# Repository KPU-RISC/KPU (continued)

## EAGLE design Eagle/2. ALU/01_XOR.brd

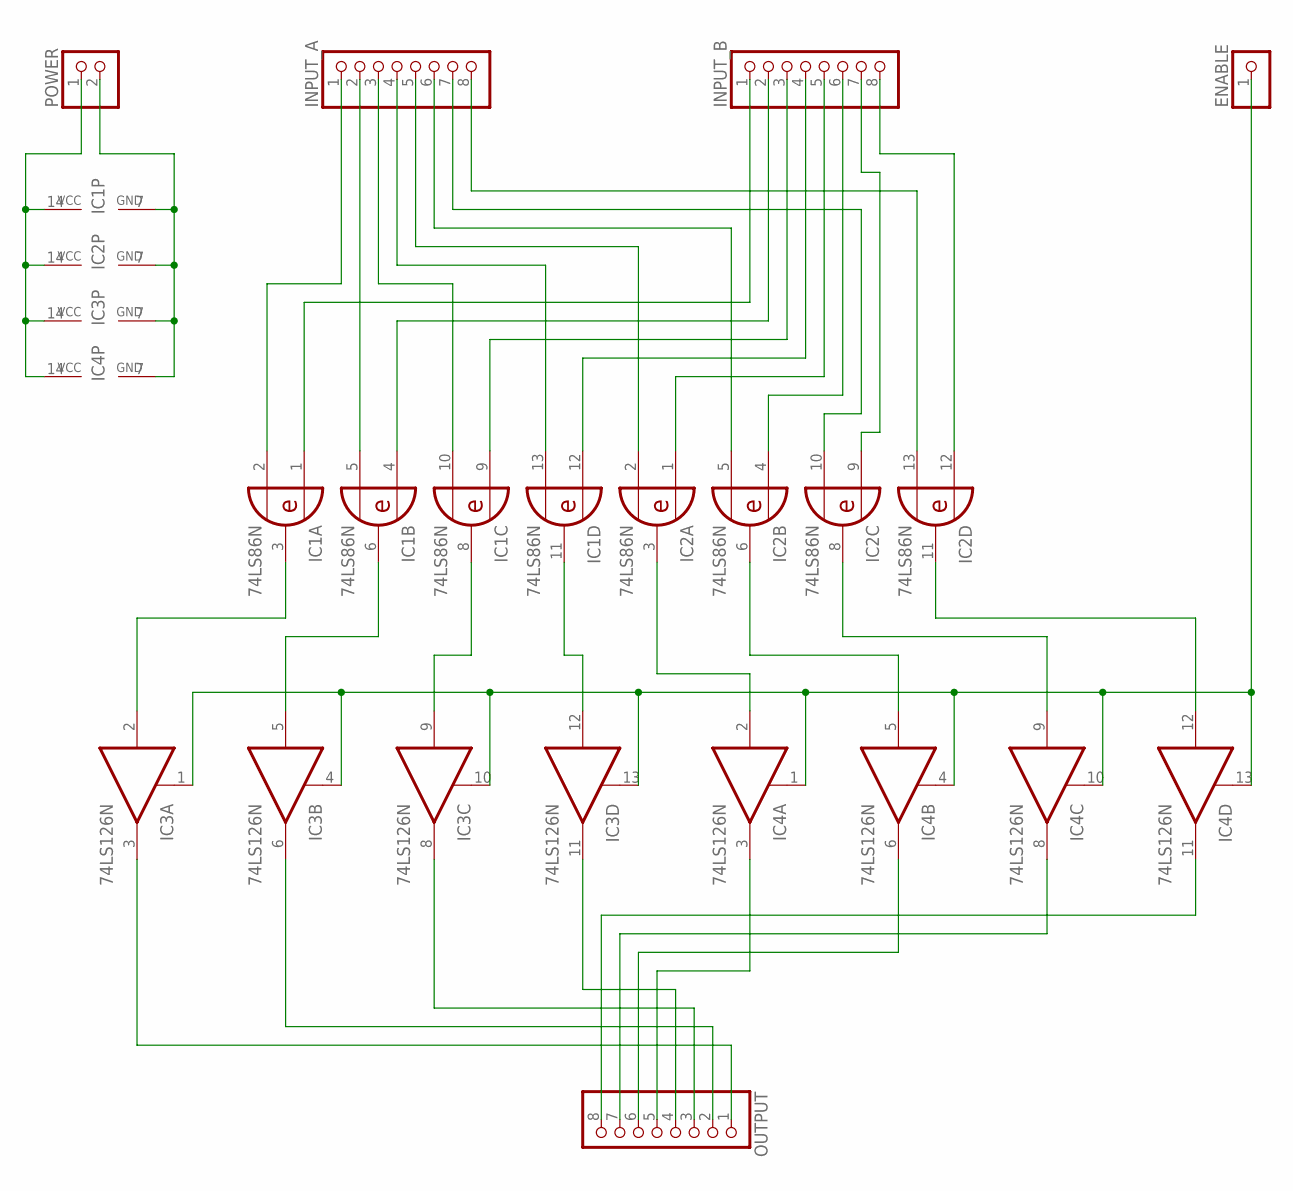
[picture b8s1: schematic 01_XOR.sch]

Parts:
ENABLE: PINHD-1X1; 1X01
IC1, IC2: 74LS86N; DIL14
IC3, IC4: 74LS126N; DIL14
INPUT_A: PINHD-1X8; 1X08
INPUT_B: PINHD-1X8; 1X08
OUTPUT: PINHD-1X8; 1X08
POWER: PINHD-1X2; 1X02

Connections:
GND: IC1.7 (GND), IC2.7 (GND), IC3.7 (GND), IC4.7 (GND), POWER.2
unnamed: IC1.2 (I1), INPUT_A.1
unnamed: IC1.1 (I0), INPUT_B.1
unnamed: IC1.5 (I1), INPUT_A.2
unnamed: IC1.4 (I0), INPUT_B.2
unnamed: IC1.10 (I1), INPUT_A.3
unnamed: IC1.9 (I0), INPUT_B.3
unnamed: IC1.13 (I1), INPUT_A.4
unnamed: IC1.12 (I0), INPUT_B.4
unnamed: IC2.2 (I1), INPUT_A.5
unnamed: IC2.1 (I0), INPUT_B.5
unnamed: IC2.5 (I1), INPUT_A.6
unnamed: IC2.4 (I0), INPUT_B.6
unnamed: IC2.10 (I1), INPUT_A.7
unnamed: IC2.9 (I0), INPUT_B.7
unnamed: IC2.13 (I1), INPUT_A.8
unnamed: IC2.12 (I0), INPUT_B.8
unnamed: IC1.3 (O), IC3.2 (I)
unnamed: IC1.6 (O), IC3.5 (I)
unnamed: IC1.8 (O), IC3.9 (I)
unnamed: IC1.11 (O), IC3.12 (I)
unnamed: IC2.3 (O), IC4.2 (I)
unnamed: IC2.6 (O), IC4.5 (I)
unnamed: IC2.8 (O), IC4.9 (I)
unnamed: IC2.11 (O), IC4.12 (I)
unnamed: IC3.3 (O), OUTPUT.1
unnamed: IC3.6 (O), OUTPUT.2
unnamed: IC3.8 (O), OUTPUT.3
unnamed: IC3.11 (O), OUTPUT.4
unnamed: IC4.3 (O), OUTPUT.5
unnamed: IC4.6 (O), OUTPUT.6
unnamed: IC4.8 (O), OUTPUT.7
unnamed: IC4.11 (O), OUTPUT.8
unnamed: ENABLE.1, IC3.1 (OE), IC3.4 (OE), IC3.10 (OE), IC3.13 (OE), IC4.1 (OE), IC4.4 (OE), IC4.10 (OE), IC4.13 (OE)
VCC: IC1.14 (VCC), IC2.14 (VCC), IC3.14 (VCC), IC4.14 (VCC), POWER.1

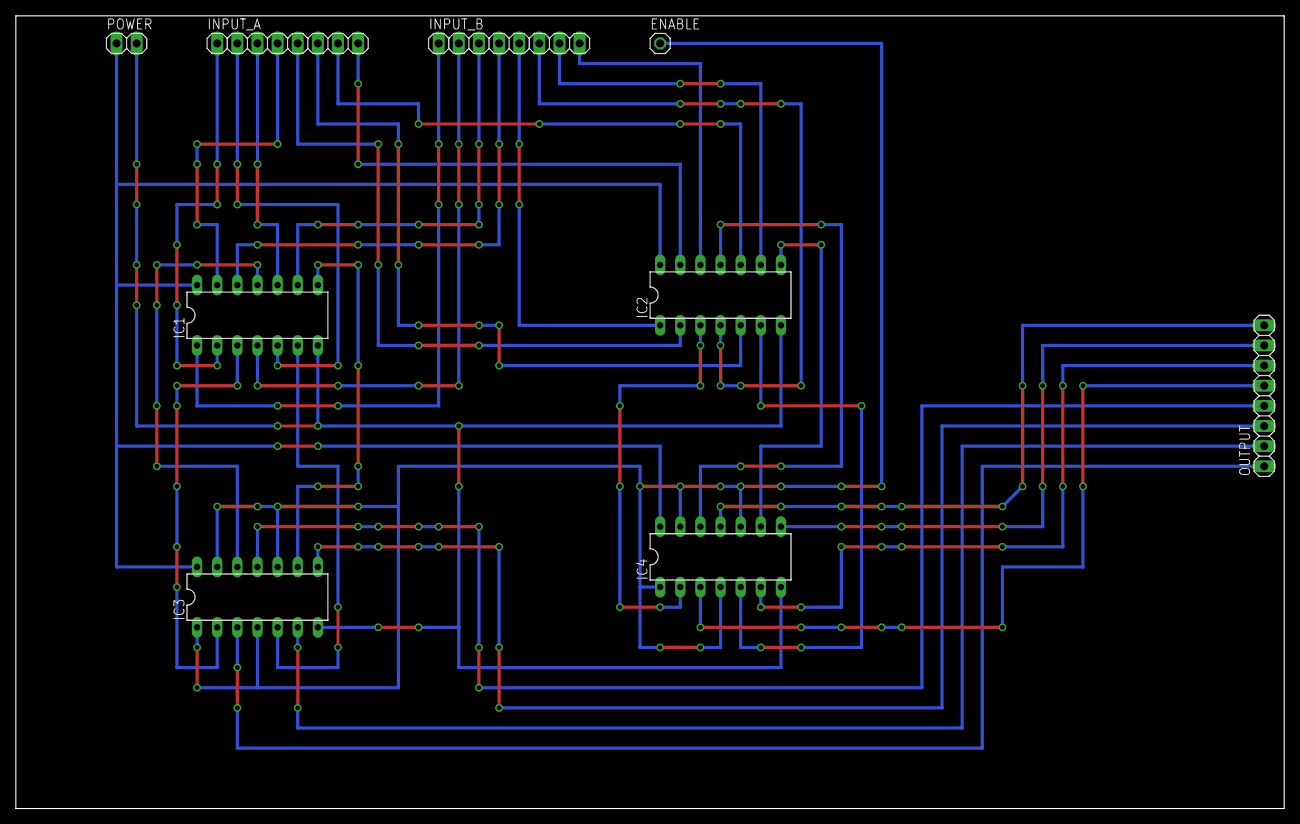
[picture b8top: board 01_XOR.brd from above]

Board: 2 copper layers, 160.0 x 100.0 mm, 9 parts (0 on the bottom side), 35 nets.
